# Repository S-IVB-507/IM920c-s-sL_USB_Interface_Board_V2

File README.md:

# IM920c/s/sL USB Interface Board V2
インタープラン株式会社のの無線モジュール、IM920c/s/sLシリーズをUSB接続するためのインターフェースボードです。\
純正品と異なる点として通電確認用LED、UARTのTx,Rxのインジケータを追加しています。\
※LEDはUARTバスに直結のため、未検証ですがボーレートを上げると信号が乱れる可能性があります。修正を検討中です。

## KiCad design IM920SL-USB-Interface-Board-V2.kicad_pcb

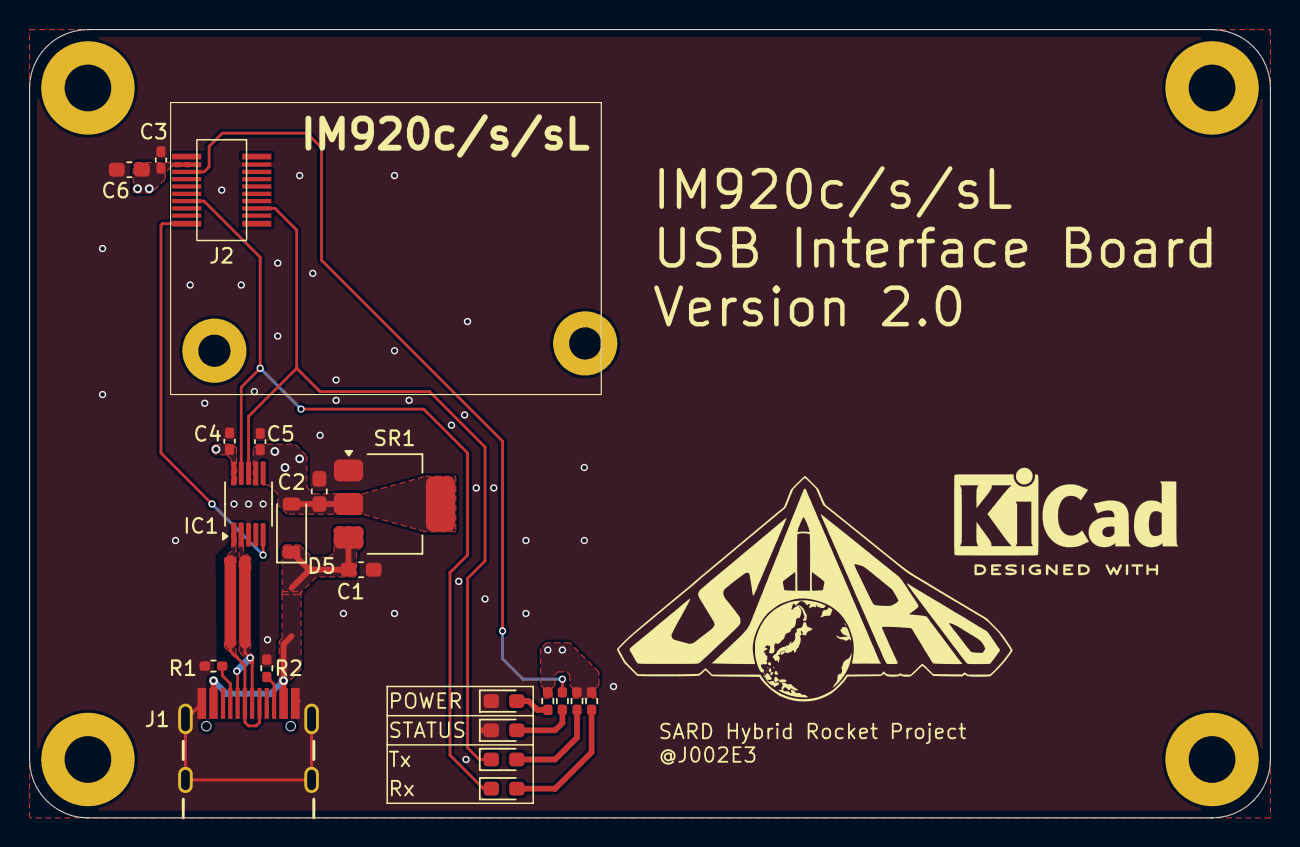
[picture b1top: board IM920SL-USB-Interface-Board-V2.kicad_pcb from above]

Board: 2 copper layers, 85.0 x 54.0 mm, 25 parts (0 on the bottom side), 15 nets.

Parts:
C1: 10uF; C_0603_1608Metric_Pad1.08x0.95mm_HandSolder
C2: 22uF; C_0603_1608Metric_Pad1.08x0.95mm_HandSolder
C3, C4, C5: 0.1uF; C_0402_1005Metric_Pad0.74x0.62mm_HandSolder
C6: DNF; C_0603_1608Metric_Pad1.08x0.95mm_HandSolder
D1, D2, D3, D4: LED; LED_0603_1608Metric_Pad1.05x0.95mm_HandSolder
D5: 30V2A?; D_SOD-123
H1, H2, H3, H4: MountingHole_Pad; MountingHole_3.2mm_M3_Pad
IC1: CH340E; MSOP-10_3x3mm_P0.5mm
J1: USB4105-GF-A; GCT_USB4105-GF-A
J2: IM920SL
R1, R2: 5.1k; R_0402_1005Metric_Pad0.72x0.64mm_HandSolder
R3, R4, R5, R6: 1k; R_0402_1005Metric_Pad0.72x0.64mm_HandSolder
SR1: AZ1117CR-3.3TRG1

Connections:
+3.3V: C2.1, C3.2, C4.2, C5.1, C6.1, D5.2 (A), IC1.7 (VCC), IC1.10 (V3), J2.17 (VCC), R4.1, R5.1, R6.1, SR1.2 (OUTPUT)
/UART_CTS: IC1.5 (~CTS), J2.1 (IO1/BUSY)
/UART_RxI: D4.1 (K), IC1.9 (RXD), J2.7 (IO7/TxD)
/UART_TxO: D3.1 (K), IC1.8 (TXD), J2.6 (IO6/RxD)
/USB_DN: IC1.2 (UD-), J1.A7 (DN1), J1.B7 (DN2)
/USB_DP: IC1.1 (UD+), J1.A6 (DP1), J1.B6 (DP2)
GND: C1.2, C2.2, C3.1, C4.1, C5.2, C6.2, D1.1 (K), D2.1 (K), IC1.3 (GND), J1.A1_B12 (GND), J1.B1_A12 (GND__1), J1.SH1 (SHELL_GND), J1.SH2 (SHELL_GND__1), J1.SH3 (SHELL_GND__2), J1.SH4 (SHELL_GND__3), J2.18 (GND), R1.2, R2.2, SR1.1 (ADJ/GND)
unnamed: D1.2 (A), R4.2
unnamed: D2.2 (A), R3.2
unnamed: D3.2 (A), R5.2
unnamed: D4.2 (A), R6.2
unnamed: J1.A5 (CC1), R1.1
unnamed: J1.B5 (CC2), R2.1
unnamed: J2.15 (STATUS), R3.1
VBUS: C1.1, D5.1 (K), J1.A4_B9 (VBUS), J1.B4_A9 (VBUS__1), SR1.3 (INPUT)

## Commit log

2025-07-16 修正
    - IM920固定用ネジの裏面マスクを削除
    - シルクスクリーン上のテキストを修正
